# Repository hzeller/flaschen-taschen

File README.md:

Noisebridge Flaschen Taschen Project
====================================

Software and Raspberry Pi interface hardware for [FlaschenTaschen].

FlaschenTaschen is inspired by projects such as the [Muro de botellas]
or [MateLight]. A bunch of Noisebridgers have seen Mate Light in action
at [32c3] and got excited :)
So our Noisebridge interpretation of it has a German influenced name.

Unfortunately, in the US, bottle reuse is not at all a thing, so there
are no standardized crates with bottles you can buy.
So we use milk crates (which is a thing) and put common, clear 12oz (355ml)
bottles in (Mate, Corona,..) inside. Wrapped in aluminum foil, they
make nice pixels.

How about watching [a movie](https://youtu.be/OEUFIpM10FE) ?

The set-up is 9 crates wide and 7 crates high for a total of
63 [crates (see wiring here)](./doc/wiring.md) with 25 'pixels' each
(this is what fits in our MakerFaire booth). 45x35 pixels or 1575 pixels total.
All operated by a Raspberry Pi that provides a [network API][protocols] to
update the display.

This is how it looks from the back:

## Sending content to FlaschenTaschen

The [client](./client) directory contains some useful utilities such as
`send-text`, `send-image` or `send-video` that you might be interested in.

Also, the current development [VLC] natively supports the FlaschenTaschen
protocol if you want to send a video.

## Tutorial: start local server and create new clients

To develop visuals for the FlaschenTaschen display once it is ready, here you
can already play around writing software that updates the networked display.

#### 1. Check out the project

```bash
$ git clone --recursive https://github.com/hzeller/flaschen-taschen.git
$ cd flaschen-taschen
```

#### 2. Compile and run local server showing content in a Terminal

If you are not around Noisebridge to directly send images to the FlaschenTaschen
installation, then you can start your own FlaschenTaschen server that displays
the pixels as colored spaces in a terminal. Note, you need a fairly recent
terminal that can display 24 Bit color (Konsole can do that for a while, more
recent Gnome terminals as well. Also, newer xterms can do that as well. If you
are on a Mac, an iTerm2 version 3.x will work).

In one terminal, go to the [server/](./server) directory, compile the
terminal-based display and run it. Make sure to have it large enough to show
all pixels:

```
$ cd server
$ make FT_BACKEND=terminal
$ ./ft-server   #  this will now show a black 'screen'
```

(looks too big on screen ? Try adding the option `--hd-terminal`)

If you want to dig into details and understand the various server
implementations, check out the [server README](./server/README.md).

#### 3. Get started with the API
FlaschenTasachen provides a [network protocol](./doc/protocols.md), but there
are also client APIs available - the [api subdirectory](./api) is the best to
inspect here.

To get started with programming, go to the
[examples-api-use/](./examples-api-use) directory, compile the programs and
run it.

```
$ cd examples-api-use
$ make simple-animation
$ ./simple-animation localhost # <- network address of display.
```

Now go back to your terminal the `ft-server` is running and you'll see the
space-invaders animation!

Easiest to get started with the programming is
to read the [simple-example.cc](./examples-api-use/simple-example.cc) code,
then move on to [simple-animation.cc](./examples-api-use/simple-animation.cc).

If you want to implement the simple network protocol in another language
[check out the protocol description](./doc/protocols.md) or look at the
[C++ implementation](./api/lib/udp-flaschen-taschen.cc).

For some immediate fun, send a PPM image to your server. Since the server
already understands that format natively, you can unleash the usual
[netpbm] toolbox for image manipulation:

```
bash$ jpegtopnm myimage.jpg | stdbuf -o64k pnmscale -xysize 45 35 > /dev/udp/localhost/1337
```

For a tool that decodes images (including animated gifs), go to
the [client/](./client) sub-directory compile `send-image`
(`make send-image`, see
[Send-Image section in client/](./client/README.md#send-image) for needed
dependencies), then run
`./send-image -h localhost some-image.png` which reads images and
sends them to the FlaschenTaschen display.

## Related Software

There are various projects that create demos for F~T. Collecting links here.
Check out these repositories:

  * https://github.com/cgorringe/ft-demos Demos such as [plasma](./img/ft-completed.jpg), lines, quilt, ...
  * https://github.com/scottyallen/flaschenvnc VNC implementation:
   cast your screen to FlaschenTaschen
   ([like so](https://www.youtube.com/watch?v=s3pGp_Vf4Pk))
  * A [FlaschenTaschen VLC output](https://git.videolan.org/?p=vlc.git;a=commit;h=cf334f257868d20b6a6ce024994e84ba3e3448c3) by François Revol.
    It is already submitted upstream, but until it hits distributions, you have
    to [compile VLC from git](https://wiki.videolan.org/UnixCompile/). That VLC
    version is >= `3.0.0-git Vetinari`.
    Then `sudo make install ; sudo ldconfig` and run it like so:
    ```
    # Here, ft.noise is the hostname of the flaschen taschen display:
    $ vlc --vout flaschen --flaschen-display=ft.noise \
          --flaschen-width=45 --flaschen-height=35 \
          <video-filename-or-YouTube-URL>
    ```
  * https://codeberg.org/alxndr42/ft-neko - Neko for FlaschenTaschen

## Connecting LED strips to the Pi

LED strips are controlled by a Raspberry Pi, connected via
a [custom level shifter](./hardware) for up to 16 strips
(of which we only need 9 for our installation right now).

[FlaschenTaschen]: https://noisebridge.net/wiki/Flaschen_Taschen
[Muro de botellas]: http://www.zuloark.com/muro-de-botellas/
[MateLight]: https://github.com/jaseg/matelight
[RGB Matrix Adapter]: https://github.com/hzeller/rpi-rgb-led-matrix/tree/master/adapter/active-3
[32c3]: https://events.ccc.de/congress/2015/wiki/Static:Main_Page
[protocols]: ./doc/protocols.md
[netpbm]: http://netpbm.sourceforge.net/
[2025-video]: https://www.youtube.com/watch?v=hs8FoROzE4M
[7of9-video]: https://www.youtube.com/watch?v=Uc2-8ntcEpY
[VLC]: https://www.videolan.org/

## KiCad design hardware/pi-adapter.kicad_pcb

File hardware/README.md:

Hardware
========

## Connecting LED strips to the Pi

LED strips are controlled by a Raspberry Pi, connected via
a custom level shifter that first has been developed for FlaschenTaschen
but is now broken out as [separate Spixels PCB and library][spixels].

This adapter to the Raspberry Pi can support up to 16 SPI LED strips (e.g. WS2801 or APA102) at once.

&nbsp;&nbsp;&nbsp;&nbsp;&nbsp;

## Pi Mounting Plate

We have the Pi in a separate crate together with one of the power supplies. It is
held in place with zip-ties through the holes of the crate using this
laser-cut mounting plate. To be easily modifyable,
[it is written in PostScript](./pi-mounting-rig.ps) and can be converted to a
[DXF file](./pi-mounting-rig.dxf) (a typical input to laser cutters)
with the Makefile.

[spixels-hardware]: https://github.com/hzeller/spixels/tree/master/hardware
[spixels]: http://spixels.org/

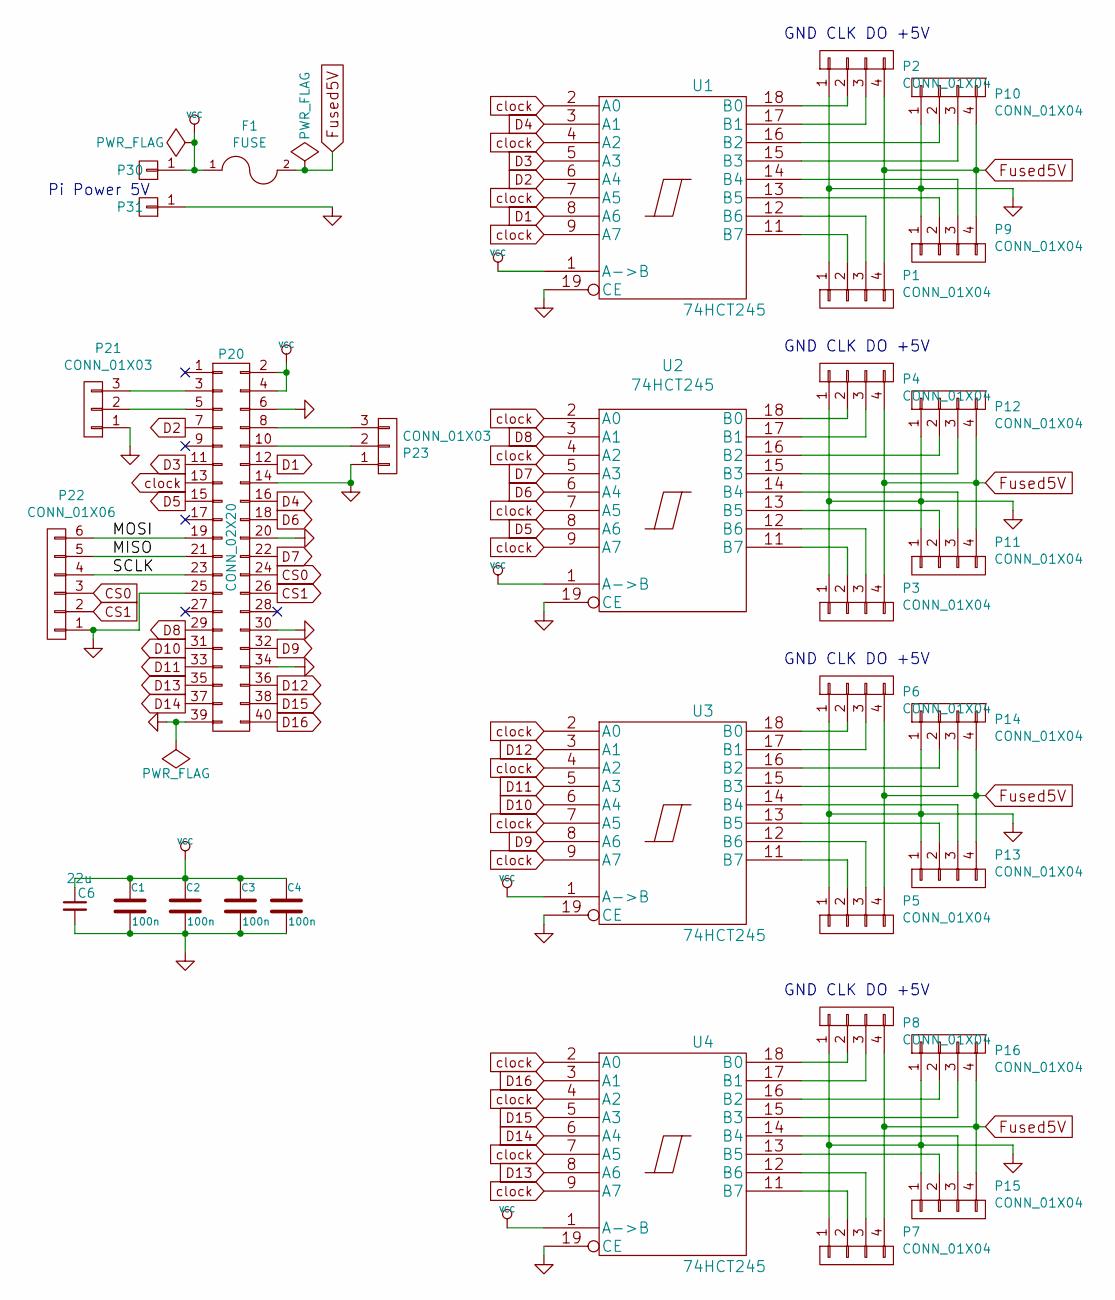
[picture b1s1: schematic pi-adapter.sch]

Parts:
C1, C2, C3, C4: 100n; C_0805_HandSoldering
C6: 22u; C_1206_HandSoldering
F1: FUSE; Fuseholder5x20_horiz_open_universal_Type-III
P1, P2, P3, P4, P5, P6, P7, P8, P9, P10, P11, P12, P13, P14, P15, P16: CONN_01X04; Pin_Header_Straight_1x04
P20: CONN_02X20; Pin_Header_Straight_2x20
P21, P23: CONN_01X03; Pin_Header_Straight_1x03
P22: CONN_01X06; Pin_Header_Straight_1x06
P30: +5V; Pin_Header_Straight_1x01
P31: GND; Pin_Header_Straight_1x01
U1, U2, U3, U4: 74HCT245; TSSOP-20_4.4x6.5mm_Pitch0.65mm

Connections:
/MISO: P20.21, P22.5
/MOSI: P20.19, P22.6
/SCLK: P20.23, P22.4
CS0: P20.24, P22.3
CS1: P20.26, P22.2
D1: P20.12, U1.8 (A6)
D2: P20.7, U1.6 (A4)
D3: P20.11, U1.5 (A3)
D4: P20.16, U1.3 (A1)
D5: P20.15, U2.8 (A6)
D6: P20.18, U2.6 (A4)
D7: P20.22, U2.5 (A3)
D8: P20.29, U2.3 (A1)
D9: P20.32, U3.8 (A6)
D10: P20.31, U3.6 (A4)
D11: P20.33, U3.5 (A3)
D12: P20.36, U3.3 (A1)
D13: P20.35, U4.8 (A6)
D14: P20.37, U4.6 (A4)
D15: P20.38, U4.5 (A3)
D16: P20.40, U4.3 (A1)
Fused5V: F1.2, P1.4, P2.4, P3.4, P4.4, P5.4, P6.4, P7.4, P8.4, P9.4, P10.4, P11.4, P12.4, P13.4, P14.4, P15.4, P16.4
GND: C1.2, C2.2, C3.2, C4.2, C6.2, P1.1, P2.1, P3.1, P4.1, P5.1, P6.1, P7.1, P8.1, P9.1, P10.1, P11.1, P12.1, P13.1, P14.1, P15.1, P16.1, P20.6, P20.14, P20.20, P20.25, P20.30, P20.34, P20.39, P21.1, P22.1, P23.1, P31.1, U1.10 (GND), U1.19 (CE), U2.10 (GND), U2.19 (CE), U3.10 (GND), U3.19 (CE), U4.10 (GND), U4.19 (CE)
unnamed: P1.2, U1.11 (B7)
unnamed: P1.3, U1.12 (B6)
unnamed: P2.2, U1.18 (B0)
unnamed: P2.3, U1.17 (B1)
unnamed: P3.2, U2.11 (B7)
unnamed: P3.3, U2.12 (B6)
unnamed: P4.2, U2.18 (B0)
unnamed: P4.3, U2.17 (B1)
unnamed: P5.2, U3.11 (B7)
unnamed: P5.3, U3.12 (B6)
unnamed: P6.2, U3.18 (B0)
unnamed: P6.3, U3.17 (B1)
unnamed: P7.2, U4.11 (B7)
unnamed: P7.3, U4.12 (B6)
unnamed: P8.2, U4.18 (B0)
unnamed: P8.3, U4.17 (B1)
unnamed: P9.2, U1.13 (B5)
unnamed: P9.3, U1.14 (B4)
unnamed: P10.2, U1.16 (B2)
unnamed: P10.3, U1.15 (B3)
unnamed: P11.2, U2.13 (B5)
unnamed: P11.3, U2.14 (B4)
unnamed: P12.2, U2.16 (B2)
unnamed: P12.3, U2.15 (B3)
unnamed: P13.2, U3.13 (B5)
unnamed: P13.3, U3.14 (B4)
unnamed: P14.2, U3.16 (B2)
unnamed: P14.3, U3.15 (B3)
unnamed: P15.2, U4.13 (B5)
unnamed: P15.3, U4.14 (B4)
unnamed: P16.2, U4.16 (B2)
unnamed: P16.3, U4.15 (B3)
unnamed: P20.3, P21.3
unnamed: P20.5, P21.2
unnamed: P20.8, P23.3
unnamed: P20.10, P23.2
VCC: C1.1, C2.1, C3.1, C4.1, C6.1, F1.1, P20.2, P20.4, P30.1, U1.1 (A->B), U1.20 (VCC), U2.1 (A->B), U2.20 (VCC), U3.1 (A->B), U3.20 (VCC), U4.1 (A->B), U4.20 (VCC)
clock: P20.13, U1.2 (A0), U1.4 (A2), U1.7 (A5), U1.9 (A7), U2.2 (A0), U2.4 (A2), U2.7 (A5), U2.9 (A7), U3.2 (A0), U3.4 (A2), U3.7 (A5), U3.9 (A7), U4.2 (A0), U4.4 (A2), U4.7 (A5), U4.9 (A7)

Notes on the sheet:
Pi Power 5V
GND CLK DO +5V

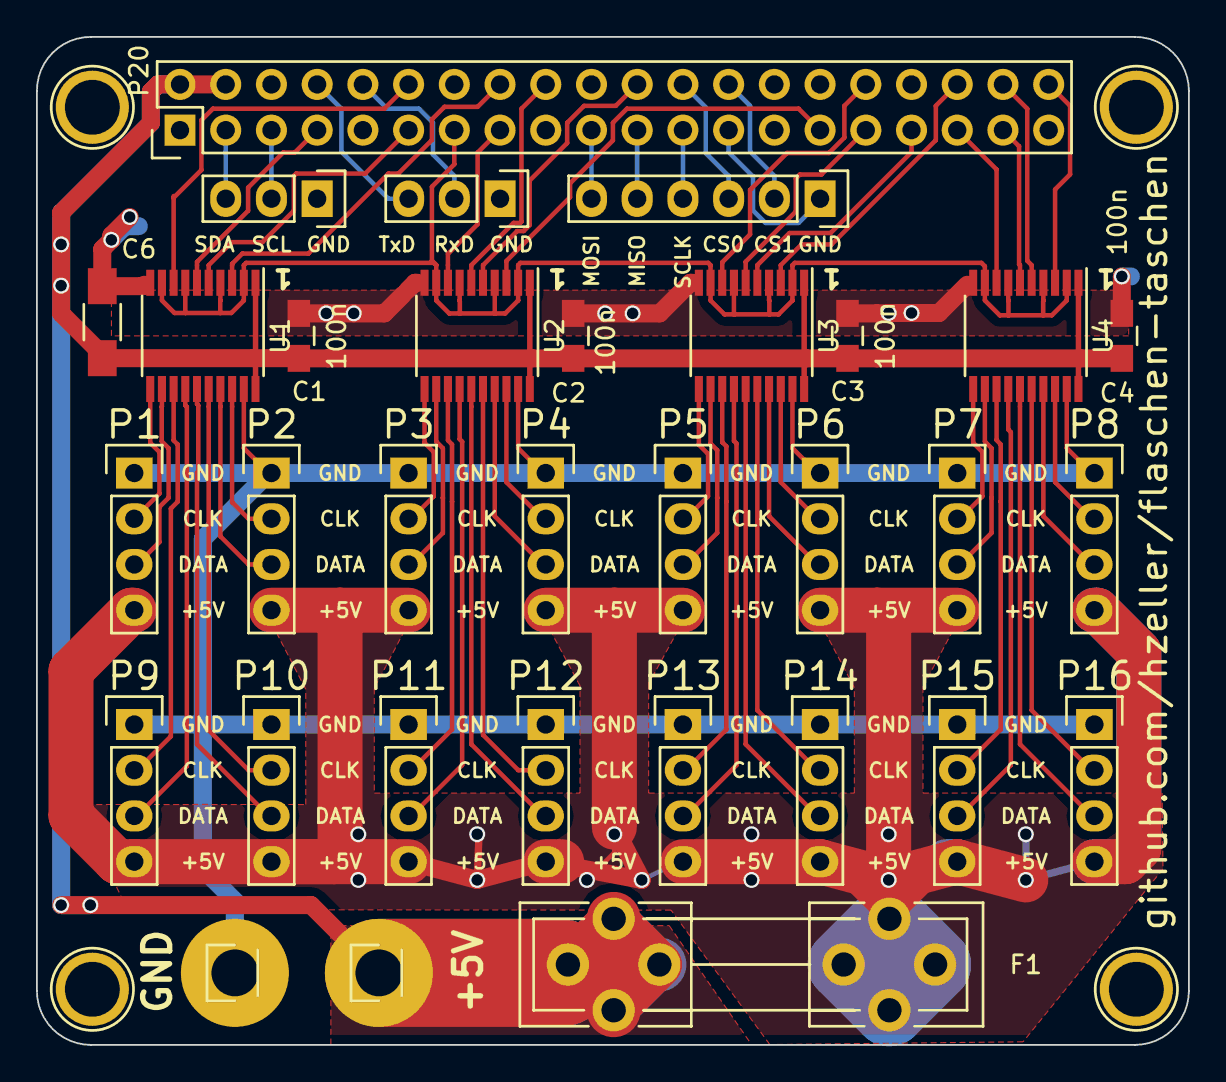
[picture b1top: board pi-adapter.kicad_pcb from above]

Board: 2 copper layers, 64.0 x 56.0 mm, 36 parts (0 on the bottom side), 61 nets.

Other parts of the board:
P40, P40#2, P41, P43: CONN_01X01; 1pin

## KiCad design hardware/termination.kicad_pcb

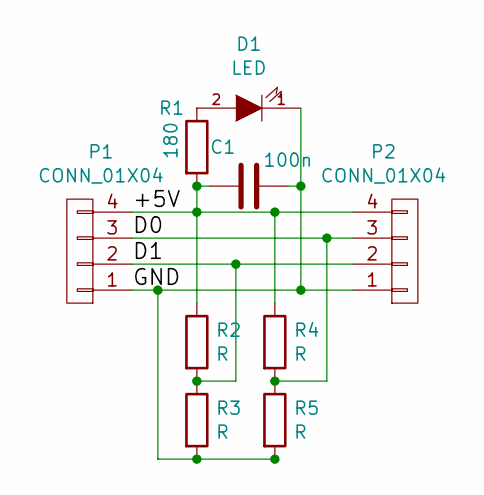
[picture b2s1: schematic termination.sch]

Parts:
C1: 100n; C_0805
D1: LED; LED-0805
P1: CONN_01X04; Pin_Header_Straight_1x04
P2: CONN_01X04; Pin_Header_Angled_1x04
R1: 180; R_0603_HandSoldering
R2, R3, R4, R5: R; R_0603_HandSoldering

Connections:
/+5V: C1.2, P1.4, P2.4, R1.2, R2.1, R4.1
/D0: P1.3, P2.3, R4.2, R5.1
/D1: P1.2, P2.2, R2.2, R3.1
/GND: C1.1, D1.1 (K), P1.1, P2.1, R3.2, R5.2
unnamed: D1.2 (A), R1.1

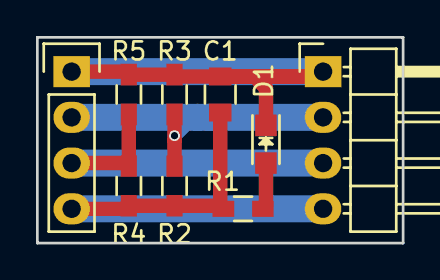
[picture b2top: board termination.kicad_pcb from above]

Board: 2 copper layers, 20.3 x 11.4 mm, 9 parts (0 on the bottom side), 5 nets.

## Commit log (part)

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2016-02-17 o daemon() does not work as well.
2016-02-17 o update doc suggesting how to connect to local servers.
2016-02-17 o Force UDP4 family for now.
2016-02-17 o Fix typo.
2016-02-18 o Make UDP server understand PPM files. That way, it properly knows how wide/high images are. Clients don't need to know exactly how big the display is.
2016-02-18 o Streamline documentation and focus on simple tutorial to get started.
2016-02-20 o Make interface choice mandatory for PixelPusher (and pass in which interface is needed). o Exit when initialization of servers don't work.
2016-02-20 o Refine README and protocols.md
2016-02-20 o update schematic image.
2016-02-20 o Bit wider power input.
2016-02-21 o mmh, looks like pnm tools have to be explained.
2016-02-22 o Less vias where text is. o Moar copper.
2016-02-22 o Add -v flag: don't show chatty video information by default.
2016-02-23 o work around ancient ffmpeg version headers.
2016-02-24 o Reset layer to 0 after drawing on it, in case the non-default servers get to use the display in-between. o smallish comment updates.
2016-02-24 o Don't use r_frame_rate that doesn't seem to exist everywhere.
2016-02-25 o The future is now: IPv6! :)
2016-02-25 Hint to use X11/xterm on Mac OSX
2016-02-25 o Provide hint in error message.
2016-02-25 o Doh': serial interface connection was off by one pin.
2016-02-26 o make it possible to provide F~T display hostname as well via environment variable.
2016-02-26 o move display updating into separate thread; all what is does is updating. That allows for better predictability of pauses.
2016-02-27 o Be a bit more economical with code lines.
2016-03-05 o Now that we have defined shutdown, we can affort to disable the cursor as we have a chance to re-enable it in the end.
2016-03-05 o Move priority updater in its own delegator class
2016-03-06 o Make main easier discoverable by renaming ft-server-main.cc -> main.cc
2016-03-06 o Also reference Schweppes display as previous project-of-this-kind. o Link Flaschen Taschen logo back to Noisebridge wiki. o The level shifting board is now in production; change text accordingly.
2016-03-06 o Get rid of jpeg artifacts in F~T logo.
2016-03-06 o Anothe rinstance of old naming.
2016-03-06 o TerminalFlaschenTaschen: only clear screen if we actually have been operating before. Otherwise we just cover up error messages.
2016-03-12 o forgotten file.
2016-03-13 o Apply patch by Patrice Levesque
2016-03-13 o Fix messed up start of file.
2016-03-13 o Provide a way to not scroll.
2016-03-13 o Add -l (layer option) to separately choose layer.
2016-03-13 o Clarify resolution of RGB display.
2016-03-13 o Added heart symbol to 5x5 font.
2016-03-13 Fixed >
2016-03-13 Implemented | ~ } { `
2016-03-14 o Check completeness of argument first before opening socket.
2016-03-14 o Simplify: remove support for WS2811 as we couldn't update these in a reasonable frame rate (and we only could use one IO port anyway).
2016-03-15 o fix some 5x5 characters.
2016-03-26 o Add BOM.
2016-03-26 o Better error handling for layer arguments.
2016-03-27 o Update doc for wiring.
2016-03-30 two small typo fixes
2016-04-03 o Fix parameter sequence.
2016-04-23 o Adapt defaults to kleine flaschen taschen 25x20
2016-04-23 o Little clarification.
2016-04-23 fixed overlapping
2016-04-23 random ball direction, fixed speed, code prettier
2016-04-24 o Put pong game in one cc file, no header needed. o smallish cleanups.
2016-04-24 o Make larger steps to better be able to do things with keyboard.
2016-04-24 o Little fiddling.
2016-04-25 fixed uninitialization of speed and pos limits
2016-04-25 removed useless space
2016-04-27 client and server works, we need to fix the physics because it really sucks.
2016-04-28 o some more smooth compile.
2016-04-29 o make a library for easier use.
2016-05-03 o Update imagery.
2016-05-04 o Provide some options for pong game.
2016-05-04 o React to Ctrl-C in two differnt ways.
2016-05-04 o Make large FlaschenTaschen wiring setup the default.
2016-05-05 o fix dependencies.
2016-05-06 o Make library objects -fPIC
2016-05-06 add option to rotate glyphs for vertical bannery style text scrolling
2016-05-06 o Read/modify/write to uncached memory is pretty slow. Do everything in CPU-cached memory and memcpy at the end.
2016-05-07 logic for rot glyph conditions todos o fix disappearing text
2016-05-07 edit help to include rotate option, edit README to include example
2016-05-07 add option to rotate glyphs for vertical bannery style text scrolling
    logic for rot glyph conditions
    todos
    o fix disappearing text
    fix width and height offsets to fix disapperaing text
    edit help to include rotate option, edit README to include example
    edit height default value, edit RotDrawText for loop conditions and argument to RotDrawText
2016-05-07 o Some more renaming needed.
2016-05-08 o Update image to full installation
2016-05-09 o use VerticalDrawText() for a vertical banner of text scrolling from bottom to top o uses CharacterWidth of 'W' from bdf-font for font width, does not assume flaschen taschen dimensions
2016-05-09 remove whitespace
2016-05-09 adds send-text option, comments, and readme examples enabling vertical bannery style text scrolling
    * VerticalDrawText() scrolls text from bottom to top
    * use CharacterWidth of 'W' from bdf-font for font width, does not assume
    flaschen taschen dimensions
2016-05-09 fix indentation alignment
2016-05-09 vertical/horizontal example should run at once on different layers
2016-05-10 fix two problems: o calculate total_height correctly using VerticalDrawText (test with non square fonts) o add font.height() offset to Y starting point when scrolling vertically
2016-05-11 o Add reference to VNC implementation.
2016-05-14 o Move commandline parsing into game engine for simpler game implementation. o Show on screen the player connect. o Use absolute game time in game. o Don't need Timer class anymore. o Smallish cleanu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
2016-05-15 o Add FPS output to terminal output.
2016-05-15 o When a client exits, tell the game-engine. o Game-engine restarts game and gathers new players when we lost a gamer.
2016-05-15 o Clean display at the right time
2016-05-15 fixed the countdown block
2016-05-15 o Simplify main README (submodules are not needed for the usual case)
2016-05-15 o Fix counting.
2016-05-16 o Don't update display if all pixels have been send to invisible layers.
2016-05-19 Fix recvfrom on Mac OS.
    On Mac OS, recvfrom(NULL, 0) returns immediately, which breaks the game engine
    logic. recvfrom(&c, 1) instead, which blocks until the first message.
2016-05-20 o Add some DrawLine(), DrawCircle() o Add motion blur to pong ball movement.
2016-05-20 o Add a timeout mode.
2016-05-22 Add negative bound checking.
2016-05-22 Use width and height in the example.
2016-05-22 Fix vestigial method calls
2016-05-22 Correctly set emacs settings.
2016-05-24 Add *.pyc to .gitignore
2016-05-24 Prefix private variables with an underscore.
2016-05-30 o Link spixels library which is the externalized part of the MultiSPI and hardware lib.
2016-05-31 o Move crate-mapping into crate-column-flaschen-taschen (only place where it is needed now). o rename rgb-flaschen-taschen to rgb-matrix-flaschen-taschen
2016-06-04 o Use AV_PIX_... instead of PIX_... constants. (Thanks to @jaseg)
2016-06-04 o Some readme tweaks.
2016-06-04 o Limiting size of buffer is not a-priori a good idea, as it might just be used as a buffer.
2016-06-07 Add a Bookcase class to give a 2d pixel mapping to the bookcase leds.
    Also add a rainbow animation to demonstrate it.
2016-06-07 Animation to fade all Flaschens in the space through all the colors at once.
2016-06-07 Bookcase animation to show off the golden spiral design.
2016-06-07 Add sample animation for noise square table
2016-06-09 o Remove unnecessary old experiments.
2016-06-16 o Add outline mode, in which we can choose a color of the outline of a font. Nice to create contrasty text without plastering everything with a background.
2016-06-16 o Add unicode replacement character � o Add unicode for 'full block' (decimal 9608)
2016-06-17 o Separate pong out of the main binaries (requires Linux specific joystick lib)
2016-06-23 o Avoid snprintf() in SetPixel() reduced CPU requirements by roughly 50%.
2016-07-24 o Proper parent for RGB Matrix flaschen taschen.
2016-07-24 o Documentation maintenance.
2016-08-01 o Terminal mode does never make sense to run as daemon
2016-08-01 o Correct calculation of column-height
2016-08-01 o a little bit re-organization.
2016-08-01 o Update some READMEs
2016-08-01 o Readme tweaks
2016-08-06 o Add Makefile to generate dxf out of postscript.
2016-08-06 o Point out VLC in the send-video option.
2016-08-28 o remove unnecessary whitespace; add PDF->dxf conversion.
2016-10-15 o Allow to scroll in opposite direction.
2016-12-10 o RGBMatrix: determine size by default from the matrix properties unless explicitly overridden. o Remove unnecessary crate-simulation spacing code.
    Fixes #25 - there the geometry had to explicitly set to the matrix
    geometry, which now will go automatic.
2016-12-10 o if there is no animation delay set: use a more reasonable default of 10ms (instead of 1ms).
2016-12-11 o Update of sub-project.
2016-12-19 o update default from older times
2017-01-16 o correct some links. o Update documentation.
2017-05-31 Add python example (and change API to support Python 3)
2017-06-01 Add source via webpage
2017-06-01 Remove the right bloody file
2017-07-30 o Fix proportional fonts. o Allow to show fonts that are wider than 32 pixels. Fixes #30
2017-08-01 o Newer versions of avlib want network explicitly initialized.
2017-08-22 Simplify inttypes.h include.
2018-01-22 Update rgb-matrix to latest upstream.
2018-03-27 Update led matrix.
2018-04-06 send-video: new -c clear after playing option, extra verbose option
    - now -c optionally clears the display after finishing playing videos
    - the verbose flag -v is now stackable (-vv) for more verbose output
    - reworked simpler looping logic
    - clear/documented return status for PlayVideo, main function
2018-05-10 Update to latest version of sub-modules.
2018-10-21 A lot of enhancements to the wonderful flaschen-taschen project: - possible to send directly images in python - images are encodes as png to avoid udp packet size problems - c++ framework has now dep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
2018-10-24 initialization of ptr inside q7 image type bracket
2018-11-12 Added tcp suppprt with compiling parameter UDP=tcp. Internally for every new socket connection a new thread will be created.
    Also new compiling parameter is CONSTANT_FPS=X. Where X can be any positive number.
    This is needed if multiple clients sending pictures to server at once.
    If X=0 the server is trying to show everny image received, which can lead to
    artifacts on the display.
2018-11-22 fix(examples-api-use): fix make simple-animation for Darwin systems.
    use -install_name flag instead of -soname when running on Darwin based
    systems.
2018-12-16 Made a Zombies game. Reordered directories a bit.
2018-12-27 Update README.md
    changed the readme file
2019-01-01 bugfix in server/servers.cc buffer array has to be cleared every loop
2019-07-24 3 makes -> make -k ...
2019-07-24 Added client/debian_make_all.sh, which installs deps and makes all 3 binaries (#49)
    * Added client/debian_make_all.sh, which installs deps and makes all 3 binaries
    * debian_make_all.sh: graphicsmagick-libmagick-dev-compat -> g++ libgraphicsmagick++1-dev
    * debian_make_all.sh: apt install g++ -> build-essential
2019-07-26 Add -i option to provide a text file as input. Fixes #50
2019-09-29 Update submodules to latest version. (Fixing https://github.com/hzeller/rpi-rgb-led-matrix/issues/900 )
2020-03-16 Update matrix submodule.
2020-03-19 Better highlight the packet boundaries.
2020-03-21 Fix calculation of target scale buffer.
    The buffer needs to be the size of the resulting target image not
    the original image; this workeds by accident as the target image is
    typically smaller than the video.
2020-11-19 Use latest version of rgb-matrix library.
    Fixes #56
2022-06-29 Add an array interface to Flaschen.
    Allows Numpy to be used to read and write pixel data to the buffer.
    This is typically fast and allows all features of Numpy to be used.
2022-07-01 Fix Python example to support Python 3.
    `xrange` replaced with `range`.
    Division replaced with floor division operators.
2022-07-05 Use combined header for the _data block.
2022-07-05 Add send_array method to the Python API. (#67)
    * Add send_array method.
    This method allows for arbitrary offsets and sizes.
    Refactored header and footer strings. These are no longer ever non-bytes, so conversions are no longer needed.
    * Use combined header for the _data block.
    * Rearrange bytearray size math to be more readable.
    * Remove unused header and footer strings.
2022-07-05 Setup a Flit package for the Python API.
    This provides a standard way to install the script.
    Flit is chosen since the script is small, this can be changed if needed.
2024-08-18 Update rpi-rgb-led-matrix submodule.
2024-08-18 Add shell.nix for easier dependency fetching.
2024-08-19 Add a FYI verbose message showing how many bytes were sent.
